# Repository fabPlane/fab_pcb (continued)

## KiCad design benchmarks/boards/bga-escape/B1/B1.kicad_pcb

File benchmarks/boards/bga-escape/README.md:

# Four-layer BGA escape fixtures

B1 and B2 contain 100 BGA balls connected to 100 perimeter pads on a 50 × 50 mm
board. Both use four signal copper layers and the same seed-19 shuffled target
assignment. B1 has 0.8 mm pitch and 0.35 mm square ball pads; B2 has 0.65 mm pitch
and 0.25 mm pads. These synthetic MIT fixtures need no footprint libraries.
Parameters are recorded in `manifest.json`; generated geometry is checked in.

All 200 pads are front-side SMD. There are no tracks, vias, zones, keepouts,
differential pairs or length constraints. Routing feasibility has not been
established. Native boards use KiCad default rules; the matching SRJ declares
0.15 mm minimum trace width. These are different constraint models and should
be measured separately. An unrouted input with zero native violations is not
a successful routed result.

This directory is an optional corpus for engine development. It does not add
cases to, or change the scoring of, the frozen `benchmarks/autorouter` suite.

From the repository root, regenerate and validate:

```sh
python3 benchmarks/boards/bga-escape/generate.py
/usr/bin/python3 benchmarks/boards/bga-escape/validate.py \
  --out /tmp/bga-escape-validation --repeats 3
```

`generate.py` needs only Python's standard library. `validate.py` additionally
needs KiCad's `pcbnew` Python module and `kicad-cli` on PATH. It regenerates in
a temporary directory and requires byte-identical native/SRJ files, four copper
layers, 100 two-terminal nets, 200 front-side SMD pads, no prior routing/zones,
and matching native/SRJ pad positions, sizes and net ownership. It runs native
DRC on both bundled and regenerated boards with a 180-second per-call timeout.
Each report must include errors and warnings, have zero violations and exactly
100 unconnected items, and name each expected net exactly once. Every open must
join its two actual fixture pads, matching reference, pad number, net and position.
UUIDs must be unique within the report; they are not compared across loads because
the source files omit UUIDs and KiCad assigns them when loading.

Run the regression tests (geometry tests require KiCad’s Python module):

```sh
/usr/bin/python3 -m unittest discover -s benchmarks/boards/bga-escape -p 'test_*.py'
```

The audit rejects duplicated/missing nets, unknown/repeated pads, mixed endpoints,
incorrect positions or names, incomplete severities and native errors. This checks
input evidence only and does not change routing scores or the frozen suite.

Raw reports and `summary.csv` are written only to `--out`. A failed check raises
an error and publishes no summary. To compare an earlier fixture directory with
the same `B1/` and `B2/` layout, add `--reference /path/to/earlier/bga-escape`;
this also requires exact PCB/SRJ bytes and runs the same repeated DRC checks.

The generator and generated fixtures retain their original MIT copyright notice
in [LICENSE](LICENSE). The local generator entrypoint and parameter manifest
are adapted for this self-contained directory; generated bytes are unchanged.

To reproduce the controlled before/after audit using the fresh native reports:

```sh
/usr/bin/python3 benchmarks/boards/bga-escape/measure_report_audit.py \
  /tmp/bga-escape-validation /tmp/report-decisions.csv
```

This replays the previous count-only predicate and the stricter audit on the same
reports, plus 17 malformed variants of each report. It requires every genuine
report to pass and every malformed variant to fail the stricter audit.

The SRJ input validator accepts only the five top-level fields emitted by this
fixture generator. Added traces, vias, keepouts or rule fields fail validation
because this fixture audit does not validate their semantics. Extending the
fixture format requires extending the audit explicitly.

Nested connections, terminals, obstacles and obstacle centers also accept exactly
the fields emitted by the generator. Extra width, via, layer, port, clearance or
keepout metadata is rejected. The fixture audit does not interpret those added
constraints. `measure_nested_schema.py --before PREVIOUS_VALIDATE_PY --out CSV`
replays genuine inputs and 16 nested-field additions per tier (first and last
array entries), three times each, against both validator versions.

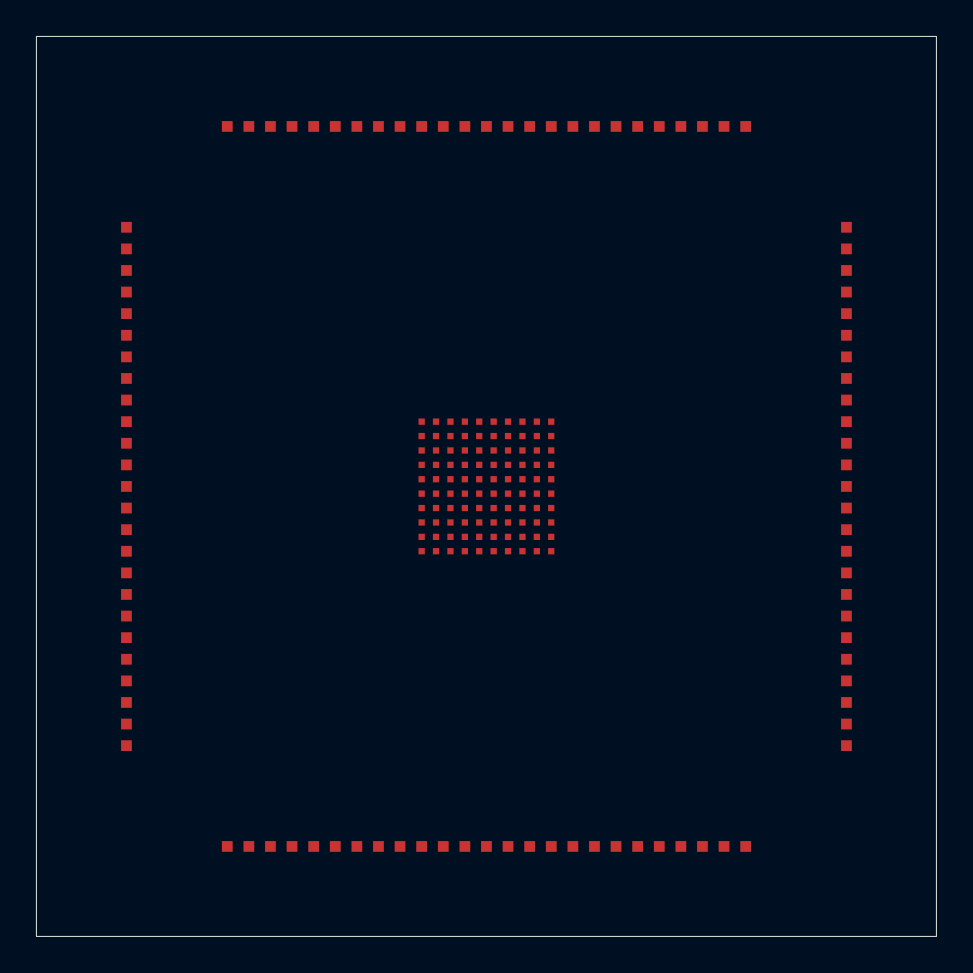
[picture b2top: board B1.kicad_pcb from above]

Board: 4 copper layers, 50.0 x 50.0 mm, 101 parts (0 on the bottom side), 100 nets, no tracks yet.

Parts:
J1, J2, J3, J4, J5, J6, J7, J8, J9, J10, J11, J12, J13, J14, J15, J16, J17, J18, J19, J20, J21, J22, J23, J24, J25, J26, J27, J28, J29, J30, J31, J32, J33, J34, J35, J36, J37, J38, J39, J40, J41, J42, J43, J44, J45, J46, J47, J48, J49, J50, J51, J52, J53, J54, J55, J56, J57, J58, J59, J60, J61, J62, J63, J64, J65, J66, J67, J68, J69, J70, J71, J72, J73, J74, J75, J76, J77, J78, J79, J80, J81, J82, J83, J84, J85, J86, J87, J88, J89, J90, J91, J92, J93, J94, J95, J96, J97, J98, J99, J100: EscapePad
U1: BGA100

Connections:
N1: J36.1, U1.1
N2: J1.2, U1.2
N3: J78.3, U1.3
N4: J17.4, U1.4
N5: J12.5, U1.5
N6: J99.6, U1.6
N7: J46.7, U1.7
N8: J33.8, U1.8
N9: J42.9, U1.9
N10: J75.10, U1.10
N11: J54.11, U1.11
N12: J28.12, U1.12
N13: J68.13, U1.13
N14: J86.14, U1.14
N15: J73.15, U1.15
N16: J97.16, U1.16
N17: J30.17, U1.17
N18: J26.18, U1.18
N19: J89.19, U1.19
N20: J58.20, U1.20
N21: J2.21, U1.21
N22: J14.22, U1.22
N23: J13.23, U1.23
N24: J21.24, U1.24
N25: J44.25, U1.25
N26: J95.26, U1.26
N27: J51.27, U1.27
N28: J9.28, U1.28
N29: J60.29, U1.29
N30: J37.30, U1.30
N31: J34.31, U1.31
N32: J40.32, U1.32
N33: J56.33, U1.33
N34: J87.34, U1.34
N35: J82.35, U1.35
N36: J38.36, U1.36
N37: J57.37, U1.37
N38: J91.38, U1.38
N39: J10.39, U1.39
N40: J79.40, U1.40
N41: J52.41, U1.41
N42: J83.42, U1.42
N43: J59.43, U1.43
N44: J3.44, U1.44
N45: J93.45, U1.45
N46: J39.46, U1.46
N47: J47.47, U1.47
N48: J35.48, U1.48
N49: J63.49, U1.49
N50: J70.50, U1.50
N51: J94.51, U1.51
N52: J16.52, U1.52
N53: J84.53, U1.53
N54: J67.54, U1.54
N55: J64.55, U1.55
N56: J23.56, U1.56
N57: J48.57, U1.57
N58: J18.58, U1.58
N59: J71.59, U1.59
N60: J4.60, U1.60
N61: J15.61, U1.61
N62: J5.62, U1.62
N63: J7.63, U1.63
N64: J62.64, U1.64
N65: J43.65, U1.65
N66: J96.66, U1.66
N67: J98.67, U1.67
N68: J92.68, U1.68
N69: J6.69, U1.69
N70: J72.70, U1.70
N71: J19.71, U1.71
N72: J20.72, U1.72
N73: J77.73, U1.73
N74: J61.74, U1.74
N75: J90.75, U1.75
N76: J74.76, U1.76
N77: J88.77, U1.77
N78: J66.78, U1.78
N79: J8.79, U1.79
N80: J41.80, U1.80
N81: J45.81, U1.81
N82: J49.82, U1.82
N83: J80.83, U1.83
N84: J31.84, U1.84
N85: J32.85, U1.85
N86: J81.86, U1.86
N87: J100.87, U1.87
N88: J50.88, U1.88
N89: J11.89, U1.89
N90: J69.90, U1.90
N91: J24.91, U1.91
N92: J65.92, U1.92
N93: J27.93, U1.93
N94: J53.94, U1.94
N95: J76.95, U1.95
N96: J22.96, U1.96
N97: J29.97, U1.97
N98: J55.98, U1.98
N99: J25.99, U1.99
N100: J85.100, U1.100

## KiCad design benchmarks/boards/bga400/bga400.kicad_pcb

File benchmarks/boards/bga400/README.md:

# Eight-layer BGA400 candidate

Original MIT synthetic fixture, seed 6408. Regenerate with:

```sh
/usr/bin/python3 -O benchmarks/boards/bga400/generate.py /tmp/bga400-new --seed 6408
bun run typecheck
/usr/bin/python3 -O benchmarks/boards/bga400/test_generate.py
FAB_ROUTER_MODULE=$HOME/bench/repos/fab_router/src/api.ts bun run test:unit
```

The destination must not exist. Requires the native `pcbnew` Python module and
`kicad-cli`. The generator checks a freshly loaded board, project rules, copper
stack, two terminals per net, absence of tracks/zones, and fresh native DRC.
It exports DSN and normalizes only the DSN root filename. Board, companion
project and DSN bytes reproduce across destination directories.

| Parameter                          |                                      Value |
| ---------------------------------- | -----------------------------------------: |
| Board                              |                                 60 × 60 mm |
| Signal copper layers               |                                          8 |
| BGA                                | 20 × 20, 0.65 mm pitch, 0.30 mm round pads |
| Destination terminals              |        400, shuffled by seed, 0.40 mm pads |
| Nets / pads / native opens         |                            400 / 800 / 400 |
| Track / clearance                  |                             0.10 / 0.10 mm |
| Through via diameter / drill       |                             0.30 / 0.10 mm |
| Native input DRC errors / warnings |                                      0 / 0 |

The companion `.kicad_pro` is part of the fixture and must travel with the board.
All copper layers are signal layers. There are no planes, pair constraints,
length groups, or external footprint libraries. The destinations form four
2 × 50 terminal banks. The permutation intentionally introduces crossings.

This expands the six-layer candidate's 324-ball, 0.8 mm BGA coverage to 400
balls at 0.65 mm pitch and 400 nets. The boards have different topology and
layer counts; routing difficulty is not established by this geometry alone.
In particular, native input admission does not establish routed feasibility or
an improvement in any engine. Production scoring and frozen fixtures are unchanged.

This candidate is outside the frozen autorouter suite. It is not registered in
that suite and does not change historical scores.

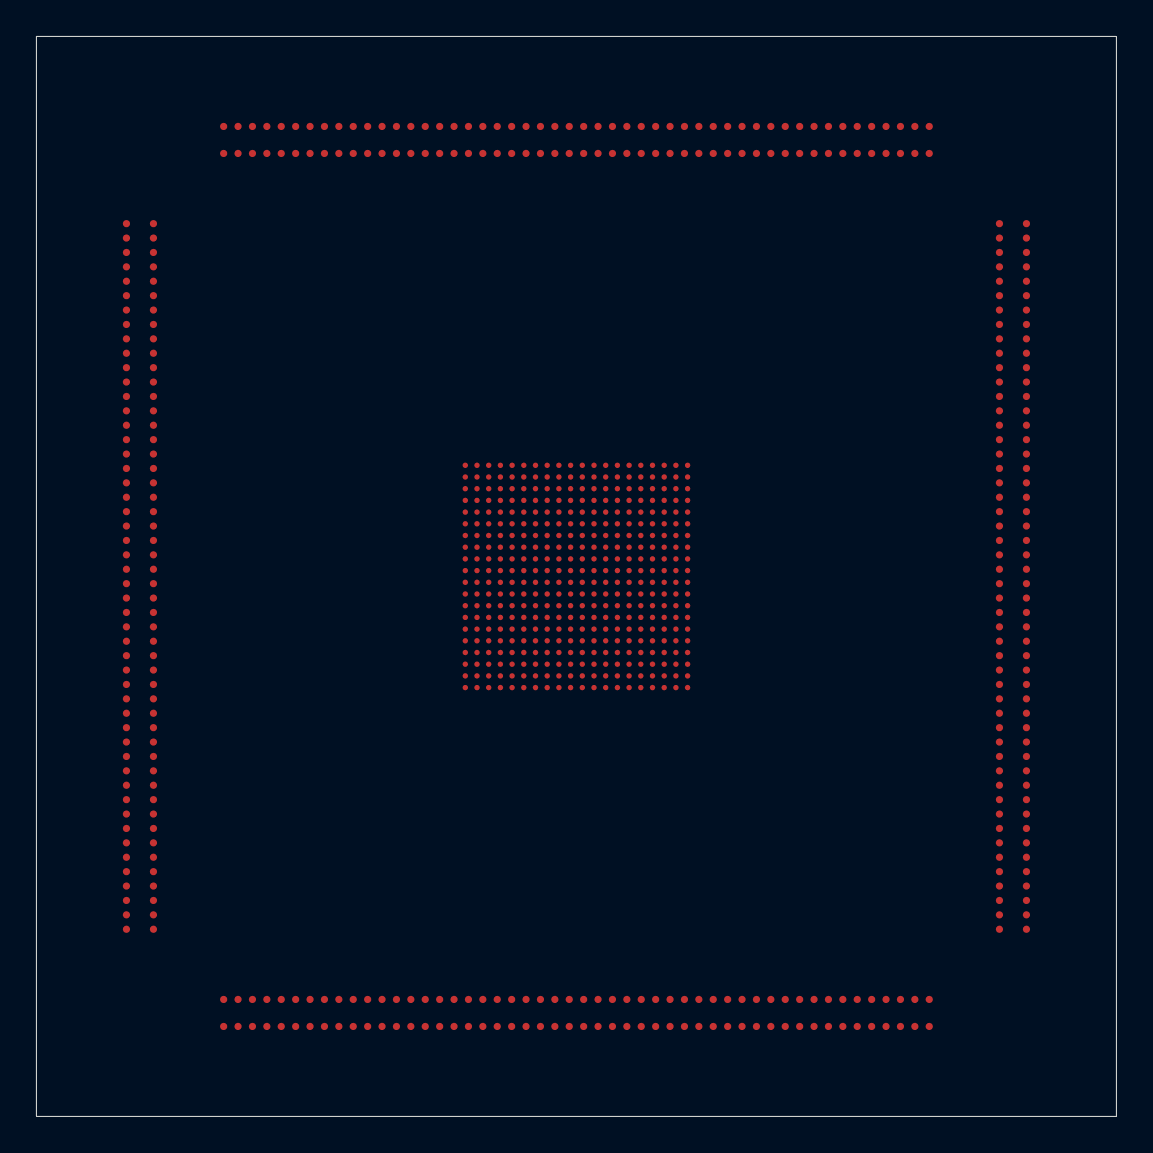
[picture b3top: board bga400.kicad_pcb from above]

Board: 8 copper layers, 60.0 x 60.0 mm, 401 parts (0 on the bottom side), 400 nets, no tracks yet.

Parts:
J1, J2, J3, J4, J5, J6, J7, J8, J9, J10, J11, J12, J13, J14, J15, J16, J17, J18, J19, J20, J21, J22, J23, J24, J25, J26, J27, J28, J29, J30, J31, J32, J33, J34, J35, J36, J37, J38, J39, J40, J41, J42, J43, J44, J45, J46, J47, J48, J49, J50, J51, J52, J53, J54, J55, J56, J57, J58, J59, J60, J61, J62, J63, J64, J65, J66, J67, J68, J69, J70, J71, J72, J73, J74, J75, J76, J77, J78, J79, J80, J81, J82, J83, J84, J85, J86, J87, J88, J89, J90, J91, J92, J93, J94, J95, J96, J97, J98, J99, J100, J101, J102, J103, J104, J105, J106, J107, J108, J109, J110, J111, J112, J113, J114, J115, J116, J117, J118, J119, J120, J121, J122, J123, J124, J125, J126, J127, J128, J129, J130, J131, J132, J133, J134, J135, J136, J137, J138, J139, J140, J141, J142, J143, J144, J145, J146, J147, J148, J149, J150, J151, J152, J153, J154, J155, J156, J157, J158, J159, J160, J161, J162, J163, J164, J165, J166, J167, J168, J169, J170, J171, J172, J173, J174, J175, J176, J177, J178, J179, J180, J181, J182, J183, J184, J185, J186, J187, J188, J189, J190, J191, J192, J193, J194, J195, J196, J197, J198, J199, J200, J201, J202, J203, J204, J205, J206, J207, J208, J209, J210, J211, J212, J213, J214, J215, J216, J217, J218, J219, J220, J221, J222, J223, J224, J225, J226, J227, J228, J229, J230, J231, J232, J233, J234, J235, J236, J237, J238, J239, J240, J241, J242, J243, J244, J245, J246, J247, J248, J249, J250, J251, J252, J253, J254, J255, J256, J257, J258, J259, J260, J261, J262, J263, J264, J265, J266, J267, J268, J269, J270, J271, J272, J273, J274, J275, J276, J277, J278, J279, J280, J281, J282, J283, J284, J285, J286, J287, J288, J289, J290, J291, J292, J293, J294, J295, J296, J297, J298, J299, J300, J301, J302, J303, J304, J305, J306, J307, J308, J309, J310, J311, J312, J313, J314, J315, J316, J317, J318, J319, J320, J321, J322, J323, J324, J325, J326, J327, J328, J329, J330, J331, J332, J333, J334, J335, J336, J337, J338, J339, J340, J341, J342, J343, J344, J345, J346, J347, J348, J349, J350, J351, J352, J353, J354, J355, J356, J357, J358, J359, J360, J361, J362, J363, J364, J365, J366, J367, J368, J369, J370, J371, J372, J373, J374, J375, J376, J377, J378, J379, J380, J381, J382, J383, J384, J385, J386, J387, J388, J389, J390, J391, J392, J393, J394, J395, J396, J397, J398, J399, J400: escape
U1: escape

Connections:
N1: J209.1, U1.1
N2: J241.2, U1.2
N3: J300.3, U1.3
N4: J82.4, U1.4
N5: J96.5, U1.5
N6: J355.6, U1.6
N7: J273.7, U1.7
N8: J326.8, U1.8
N9: J151.9, U1.9
N10: J265.10, U1.10
N11: J188.11, U1.11
N12: J41.12, U1.12
N13: J215.13, U1.13
N14: J372.14, U1.14
N15: J368.15, U1.15
N16: J351.16, U1.16
N17: J290.17, U1.17
N18: J26.18, U1.18
N19: J390.19, U1.19
N20: J157.20, U1.20
N21: J337.21, U1.21
N22: J21.22, U1.22
N23: J72.23, U1.23
N24: J62.24, U1.24
N25: J172.25, U1.25
N26: J205.26, U1.26
N27: J59.27, U1.27
N28: J315.28, U1.28
N29: J98.29, U1.29
N30: J234.30, U1.30
N31: J293.31, U1.31
N32: J175.32, U1.32
N33: J149.33, U1.33
N34: J39.34, U1.34
N35: J240.35, U1.35
N36: J214.36, U1.36
N37: J253.37, U1.37
N38: J73.38, U1.38
N39: J25.39, U1.39
N40: J31.40, U1.40
N41: J327.41, U1.41
N42: J18.42, U1.42
N43: J34.43, U1.43
N44: J317.44, U1.44
N45: J150.45, U1.45
N46: J152.46, U1.46
N47: J44.47, U1.47
N48: J266.48, U1.48
N49: J378.49, U1.49
N50: J251.50, U1.50
N51: J33.51, U1.51
N52: J310.52, U1.52
N53: J248.53, U1.53
N54: J20.54, U1.54
N55: J347.55, U1.55
N56: J358.56, U1.56
N57: J190.57, U1.57
N58: J344.58, U1.58
N59: J93.59, U1.59
N60: J267.60, U1.60
N61: J195.61, U1.61
N62: J77.62, U1.62
N63: J67.63, U1.63
N64: J80.64, U1.64
N65: J119.65, U1.65
N66: J40.66, U1.66
N67: J200.67, U1.67
N68: J255.68, U1.68
N69: J383.69, U1.69
N70: J289.70, U1.70
N71: J363.71, U1.71
N72: J219.72, U1.72
N73: J314.73, U1.73
N74: J270.74, U1.74
N75: J186.75, U1.75
N76: J102.76, U1.76
N77: J85.77, U1.77
N78: J95.78, U1.78
N79: J235.79, U1.79
N80: J113.80, U1.80
N81: J367.81, U1.81
N82: J294.82, U1.82
N83: J191.83, U1.83
N84: J49.84, U1.84
N85: J304.85, U1.85
N86: J22.86, U1.86
N87: J397.87, U1.87
N88: J94.88, U1.88
N89: J280.89, U1.89
N90: J228.90, U1.90
N91: J334.91, U1.91
N92: J394.92, U1.92
N93: J278.93, U1.93
N94: J386.94, U1.94
N95: J89.95, U1.95
N96: J299.96, U1.96
N97: J396.97, U1.97
N98: J231.98, U1.98
N99: J271.99, U1.99
N100: J335.100, U1.100
N101: J252.101, U1.101
N102: J232.102, U1.102
N103: J341.103, U1.103
N104: J312.104, U1.104
N105: J81.105, U1.105
N106: J1.106, U1.106
N107: J233.107, U1.107
N108: J333.108, U1.108
N109: J291.109, U1.109
N110: J256.110, U1.110
N111: J243.111, U1.111
N112: J103.112, U1.112
N113: J385.113, U1.113
N114: J54.114, U1.114
N115: J377.115, U1.115
N116: J115.116, U1.116
N117: J331.117, U1.117
N118: J174.118, U1.118
N119: J109.119, U1.119
N120: J339.120, U1.120
N121: J90.121, U1.121
N122: J79.122, U1.122
N123: J247.123, U1.123
N124: J37.124, U1.124
N125: J165.125, U1.125
N126: J224.126, U1.126
N127: J263.127, U1.127
N128: J107.128, U1.128
N129: J53.129, U1.129
N130: J301.130, U1.130
N131: J269.131, U1.131
N132: J332.132, U1.132
N133: J199.133, U1.133
N134: J78.134, U1.134
N135: J50.135, U1.135
N136: J91.136, U1.136
N137: J131.137, U1.137
N138: J237.138, U1.138
N139: J364.139, U1.139
N140: J139.140, U1.140
N141: J185.141, U1.141
N142: J38.142, U1.142
N143: J192.143, U1.143
N144: J391.144, U1.144
N145: J321.145, U1.145
N146: J58.146, U1.146
N147: J9.147, U1.147
N148: J213.148, U1.148
N149: J352.149, U1.149
N150: J284.150, U1.150
N151: J187.151, U1.151
N152: J303.152, U1.152
N153: J262.153, U1.153
N154: J4.154, U1.154
N155: J302.155, U1.155
N156: J318.156, U1.156
N157: J376.157, U1.157
N158: J203.158, U1.158
N159: J24.159, U1.159
N160: J155.160, U1.160
N161: J244.161, U1.161
N162: J229.162, U1.162
N163: J120.163, U1.163
N164: J366.164, U1.164
N165: J170.165, U1.165
N166: J225.166, U1.166
N167: J319.167, U1.167
N168: J227.168, U1.168
N169: J86.169, U1.169
N170: J189.170, U1.170
N171: J296.171, U1.171
N172: J245.172, U1.172
N173: J395.173, U1.173
N174: J121.174, U1.174
N175: J141.175, U1.175
N176: J382.176, U1.176
N177: J283.177, U1.177
N178: J272.178, U1.178
N179: J180.179, U1.179
N180: J112.180, U1.180
N181: J106.181, U1.181
N182: J36.182, U1.182
N183: J211.183, U1.183
N184: J97.184, U1.184
N185: J236.185, U1.185
N186: J28.186, U1.186
N187: J143.187, U1.187
N188: J179.188, U1.188
N189: J114.189, U1.189
N190: J325.190, U1.190
N191: J5.191, U1.191
N192: J15.192, U1.192
N193: J71.193, U1.193
N194: J311.194, U1.194
N195: J207.195, U1.195
N196: J75.196, U1.196
N197: J208.197, U1.197
N198: J320.198, U1.198
N199: J35.199, U1.199
N200: J12.200, U1.200
N201: J153.201, U1.201
N202: J88.202, U1.202
N203: J104.203, U1.203
N204: J259.204, U1.204
N205: J226.205, U1.205
N206: J99.206, U1.206
N207: J254.207, U1.207
N208: J197.208, U1.208
N209: J69.209, U1.209
N210: J63.210, U1.210
N211: J274.211, U1.211
N212: J181.212, U1.212
N213: J342.213, U1.213
N214: J238.214, U1.214
N215: J118.215, U1.215
N216: J87.216, U1.216
N217: J313.217, U1.217
N218: J176.218, U1.218
N219: J29.219, U1.219
N220: J7.220, U1.220
N221: J292.221, U1.221
N222: J3.222, U1.222
N223: J338.223, U1.223
N224: J76.224, U1.224
N225: J360.225, U1.225
N226: J70.226, U1.226
N227: J105.227, U1.227
N228: J220.228, U1.228
N229: J345.229, U1.229
N230: J323.230, U1.230
N231: J48.231, U1.231
N232: J374.232, U1.232
N233: J164.233, U1.233
N234: J298.234, U1.234
N235: J66.235, U1.235
N236: J161.236, U1.236
N237: J133.237, U1.237
N238: J171.238, U1.238
N239: J324.239, U1.239
N240: J10.240, U1.240
N241: J147.241, U1.241
N242: J47.242, U1.242
N243: J399.243, U1.243
N244: J371.244, U1.244
N245: J384.245, U1.245
N246: J306.246, U1.246
N247: J125.247, U1.247
N248: J130.248, U1.248
N249: J356.249, U1.249
N250: J166.250, U1.250
N251: J282.251, U1.251
N252: J140.252, U1.252
N253: J400.253, U1.253
N254: J183.254, U1.254
N255: J268.255, U1.255
N256: J380.256, U1.256
N257: J309.257, U1.257
N258: J222.258, U1.258
N259: J173.259, U1.259
N260: J196.260, U1.260
N261: J336.261, U1.261
N262: J64.262, U1.262
N263: J156.263, U1.263
N264: J276.264, U1.264
N265: J308.265, U1.265
N266: J128.266, U1.266
N267: J287.267, U1.267
N268: J370.268, U1.268
N269: J249.269, U1.269
N270: J250.270, U1.270
N271: J11.271, U1.271
N272: J142.272, U1.272
N273: J16.273, U1.273
N274: J349.274, U1.274
N275: J43.275, U1.275
N276: J127.276, U1.276
N277: J279.277, U1.277
N278: J362.278, U1.278
N279: J194.279, U1.279
N280: J242.280, U1.280
N281: J239.281, U1.281
N282: J32.282, U1.282
N283: J30.283, U1.283
N284: J60.284, U1.284
N285: J340.285, U1.285
N286: J281.286, U1.286
N287: J169.287, U1.287
N288: J387.288, U1.288
N289: J223.289, U1.289
N290: J74.290, U1.290
N291: J168.291, U1.291
N292: J375.292, U1.292
N293: J193.293, U1.293
N294: J162.294, U1.294
N295: J381.295, U1.295
N296: J111.296, U1.296
N297: J307.297, U1.297
N298: J159.298, U1.298
N299: J359.299, U1.299
N300: J56.300, U1.300
N301: J357.301, U1.301
N302: J288.302, U1.302
N303: J148.303, U1.303
N304: J218.304, U1.304
N305: J182.305, U1.305
N306: J14.306, U1.306
N307: J92.307, U1.307
N308: J42.308, U1.308
N309: J277.309, U1.309
N310: J260.310, U1.310
N311: J295.311, U1.311
N312: J68.312, U1.312
N313: J2.313, U1.313
N314: J129.314, U1.314
N315: J216.315, U1.315
N316: J132.316, U1.316
N317: J137.317, U1.317
N318: J350.318, U1.318
N319: J230.319, U1.319
N320: J261.320, U1.320
N321: J65.321, U1.321
N322: J221.322, U1.322
N323: J84.323, U1.323
N324: J285.324, U1.324
N325: J19.325, U1.325
N326: J346.326, U1.326
N327: J264.327, U1.327
N328: J27.328, U1.328
N329: J135.329, U1.329
N330: J101.330, U1.330
N331: J61.331, U1.331
N332: J184.332, U1.332
N333: J202.333, U1.333
N334: J348.334, U1.334
N335: J108.335, U1.335
N336: J398.336, U1.336
N337: J163.337, U1.337
N338: J206.338, U1.338
N339: J52.339, U1.339
N340: J17.340, U1.340
N341: J379.341, U1.341
N342: J138.342, U1.342
N343: J393.343, U1.343
N344: J126.344, U1.344
N345: J123.345, U1.345
N346: J124.346, U1.346
N347: J353.347, U1.347
N348: J83.348, U1.348
N349: J286.349, U1.349
N350: J46.350, U1.350
N351: J369.351, U1.351
N352: J160.352, U1.352
N353: J316.353, U1.353
N354: J361.354, U1.354
N355: J389.355, U1.355
N356: J373.356, U1.356
N357: J136.357, U1.357
N358: J23.358, U1.358
N359: J167.359, U1.359
N360: J158.360, U1.360
N361: J388.361, U1.361
N362: J343.362, U1.362
N363: J328.363, U1.363
N364: J51.364, U1.364
N365: J258.365, U1.365
N366: J330.366, U1.366
N367: J145.367, U1.367
N368: J144.368, U1.368
N369: J134.369, U1.369
N370: J13.370, U1.370
N371: J116.371, U1.371
N372: J305.372, U1.372
N373: J257.373, U1.373
N374: J212.374, U1.374
N375: J275.375, U1.375
N376: J6.376, U1.376
N377: J177.377, U1.377
N378: J210.378, U1.378
N379: J100.379, U1.379
N380: J154.380, U1.380
N381: J217.381, U1.381
N382: J297.382, U1.382
N383: J322.383, U1.383
N384: J57.384, U1.384
N385: J110.385, U1.385
N386: J146.386, U1.386
N387: J246.387, U1.387
N388: J117.388, U1.388
N389: J329.389, U1.389
N390: J201.390, U1.390
N391: J392.391, U1.391
N392: J178.392, U1.392
N393: J55.393, U1.393
N394: J122.394, U1.394
N395: J198.395, U1.395
N396: J365.396, U1.396
N397: J45.397, U1.397
N398: J8.398, U1.398
N399: J354.399, U1.399
N400: J204.400, U1.400
